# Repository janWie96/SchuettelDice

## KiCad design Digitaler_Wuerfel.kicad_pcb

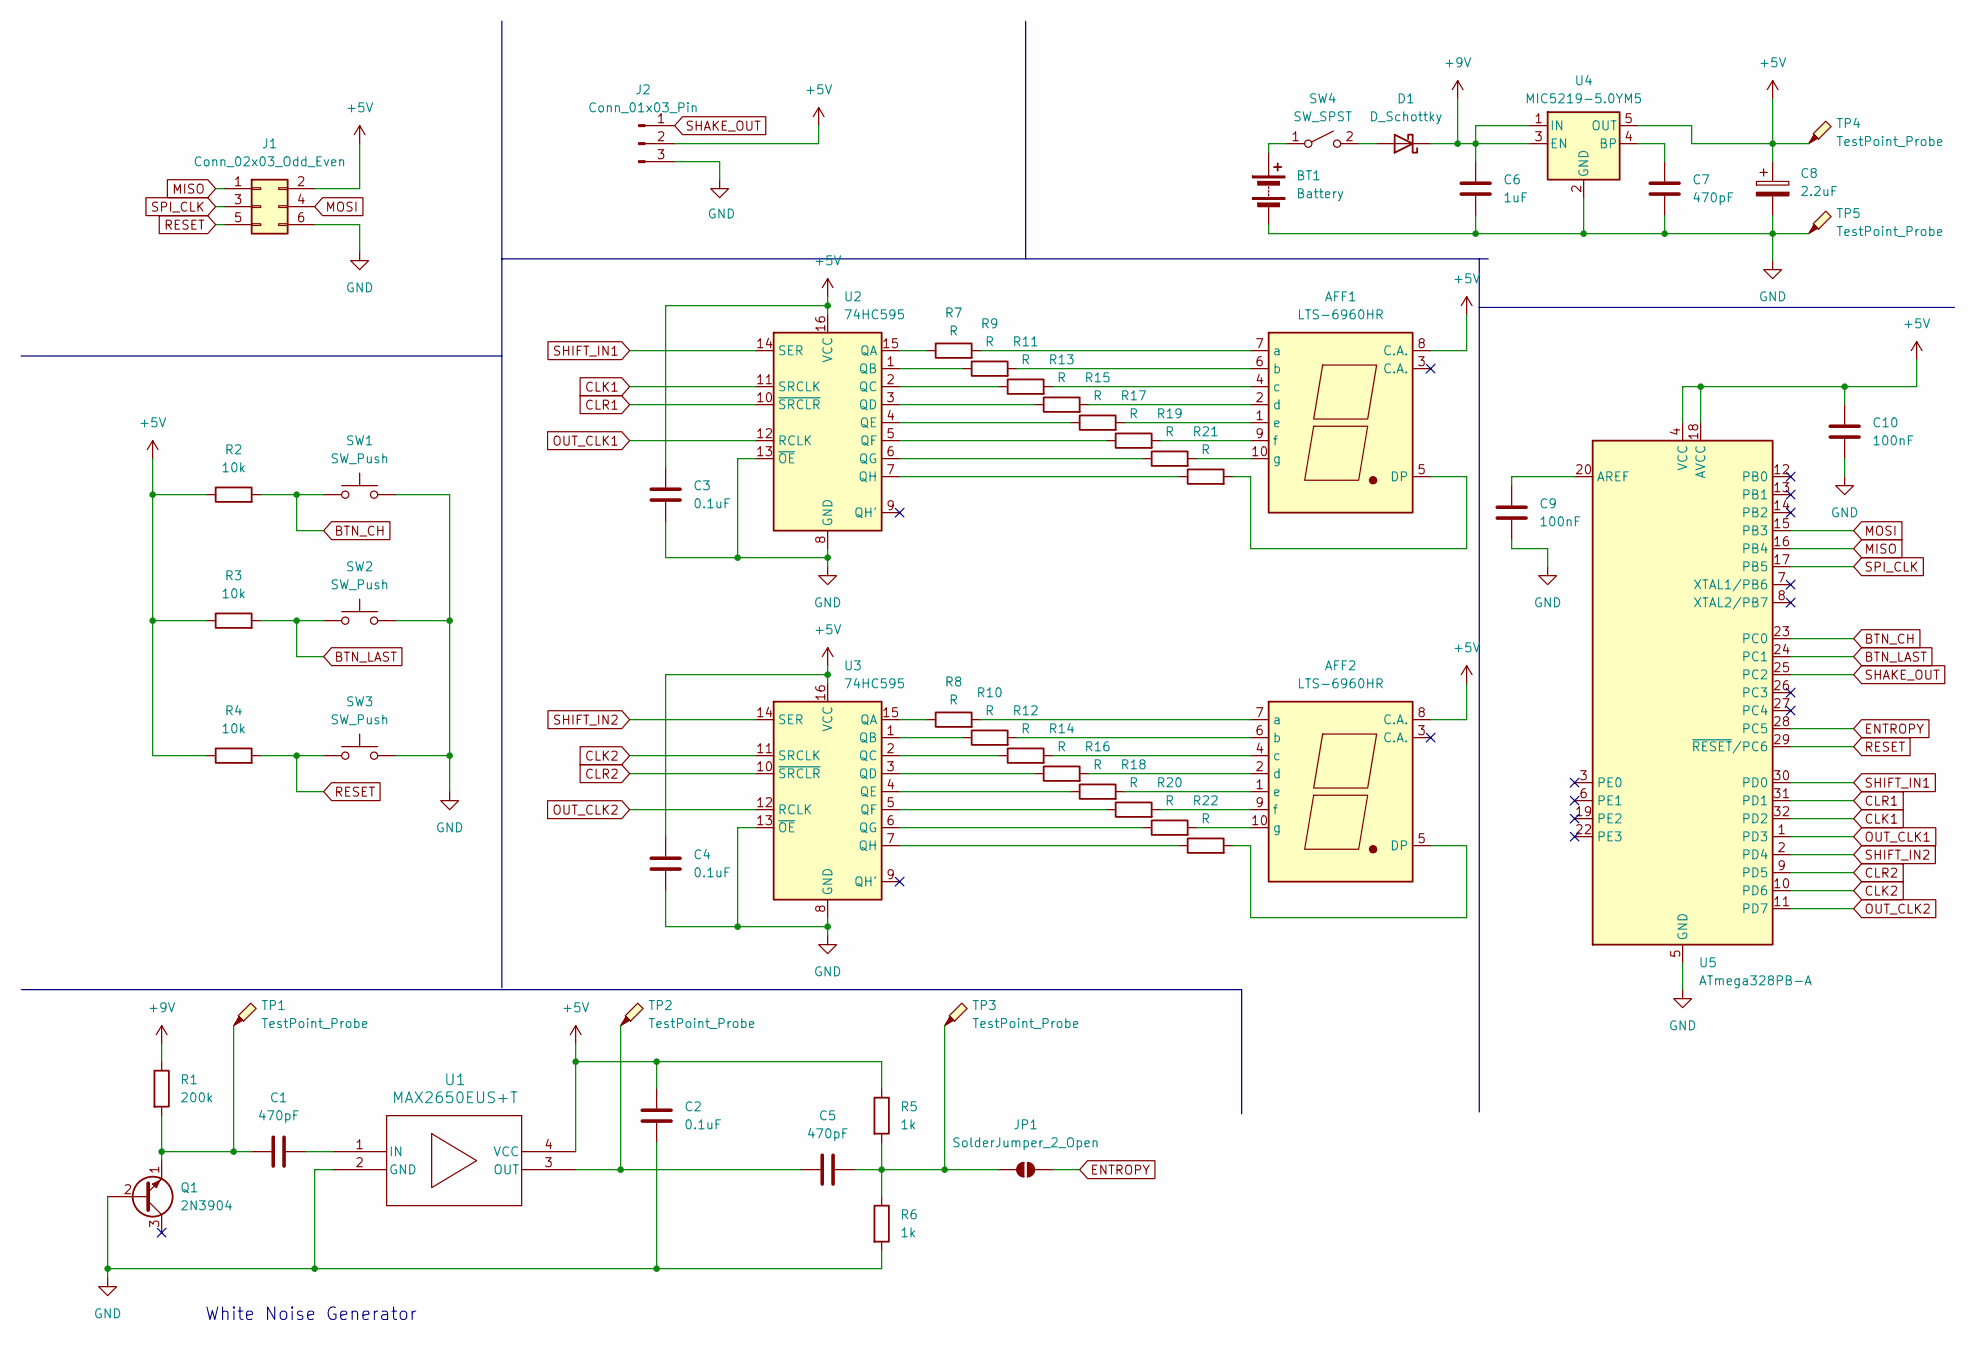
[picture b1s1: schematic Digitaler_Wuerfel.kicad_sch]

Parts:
AFF1, AFF2: LTS-6960HR; 7SegmentLED_LTS6760_LTS6780
BT1: Battery; BatteryHolder_Eagle_12BH611-GR
C1, C5, C7: 470pF; C_0805_2012Metric_Pad1.18x1.45mm_HandSolder
C2, C3, C4: 0.1uF; C_0805_2012Metric_Pad1.18x1.45mm_HandSolder
C6: 1uF; C_0805_2012Metric_Pad1.18x1.45mm_HandSolder
C8: 2.2uF; CP_EIA-3528-21_Kemet-B_Pad1.50x2.35mm_HandSolder
C9, C10: 100nF; C_0805_2012Metric_Pad1.18x1.45mm_HandSolder
D1: D_Schottky; D_SOD-323_HandSoldering
J1: Conn_02x03_Odd_Even; PinHeader_2x03_P2.54mm_Vertical
J2: Conn_01x03_Pin; PinHeader_1x03_P2.54mm_Vertical
JP1: SolderJumper_2_Open; SolderJumper-2_P1.3mm_Open_TrianglePad1.0x1.5mm
Q1: 2N3904; TO-92_Inline
R1: 200k; R_0805_2012Metric_Pad1.20x1.40mm_HandSolder
R2, R3, R4: 10k; R_0805_2012Metric_Pad1.20x1.40mm_HandSolder
R5, R6: 1k; R_0805_2012Metric_Pad1.20x1.40mm_HandSolder
R7, R8, R9, R10, R11, R12, R13, R14, R15, R16, R17, R18, R19, R20, R21, R22: R; R_0805_2012Metric_Pad1.20x1.40mm_HandSolder
SW1, SW2: SW_Push; SW_PUSH-12mm_Wuerth-430476085716
SW3: SW_Push; SW_PUSH_6mm_H5mm
SW4: SW_SPST; SW_E-Switch_EG1271_SPDT
TP1, TP2, TP3, TP4, TP5: TestPoint_Probe; TestPoint_Pad_D2.0mm
U1: MAX2650EUS+T; 21-0052F_MXM
U2, U3: 74HC595; DIP-16_W7.62mm
U4: MIC5219-5.0YM5; SOT-23-5
U5: ATmega328PB-A; TQFP-32_7x7mm_P0.8mm

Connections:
+5V: AFF1.8 (C.A.), AFF2.8 (C.A.), C2.2, C3.1, C4.1, C8.1, C10.1, J1.2, J2.2, R2.1, R3.1, R4.1, R5.1, TP4.1, U1.4 (VCC), U2.16 (VCC), U3.16 (VCC), U4.5 (OUT), U5.4 (VCC), U5.18 (AVCC)
+9V: C6.1, D1.1 (K), R1.1, U4.1 (IN), U4.3 (EN)
BTN_CH: R2.2, SW1.1, U5.23 (PC0)
BTN_LAST: R3.2, SW2.1, U5.24 (PC1)
CLK1: U2.11 (SRCLK), U5.32 (PD2)
CLK2: U3.11 (SRCLK), U5.10 (PD6)
CLR1: U2.10 (~SRCLR), U5.31 (PD1)
CLR2: U3.10 (~SRCLR), U5.9 (PD5)
ENTROPY: JP1.2 (B), U5.28 (PC5); also elsewhere on the board
GND: BT1.2 (-), C2.1, C3.2, C4.2, C6.2, C7.2, C8.2, C9.2, C10.2, J1.6, J2.3, Q1.2 (B), R6.2, SW1.2, SW2.2, SW3.2, TP5.1, U1.2 (GND), U2.8 (GND), U2.13 (~OE), U3.8 (GND), U3.13 (~OE), U4.2 (GND), U5.5 (GND), U5.21 (GND)
MISO: J1.1, U5.16 (PB4)
MOSI: J1.4, U5.15 (PB3)
unnamed: AFF1.5 (DP), R21.2
unnamed: AFF1.7 (a), R7.2
unnamed: AFF1.6 (b), R9.2
unnamed: AFF1.4 (c), R11.2
unnamed: AFF1.2 (d), R13.2
unnamed: AFF1.1 (e), R15.2
unnamed: AFF1.9 (f), R17.2
unnamed: AFF1.10 (g), R19.2
unnamed: AFF2.5 (DP), R22.2
unnamed: AFF2.7 (a), R8.2
unnamed: AFF2.6 (b), R10.2
unnamed: AFF2.4 (c), R12.2
unnamed: AFF2.2 (d), R14.2
unnamed: AFF2.1 (e), R16.2
unnamed: AFF2.9 (f), R18.2
unnamed: AFF2.10 (g), R20.2
unnamed: BT1.1 (+), SW4.1 (A)
unnamed: D1.2 (A), SW4.2 (B)
unnamed 30: C5.2, JP1.1 (A), R5.2, R6.1, TP3.1; also elsewhere on the board
unnamed: C1.1, Q1.1 (E), R1.2, TP1.1
unnamed: C1.2, U1.1 (IN)
unnamed: C5.1, TP2.1, U1.3 (OUT)
unnamed: R7.1, U2.15 (QA)
unnamed: R9.1, U2.1 (QB)
unnamed: R11.1, U2.2 (QC)
unnamed: R13.1, U2.3 (QD)
unnamed: R15.1, U2.4 (QE)
unnamed: R17.1, U2.5 (QF)
unnamed: R19.1, U2.6 (QG)
unnamed: R21.1, U2.7 (QH)
unnamed: R8.1, U3.15 (QA)
unnamed: R10.1, U3.1 (QB)
unnamed: R12.1, U3.2 (QC)
unnamed: R14.1, U3.3 (QD)
unnamed: R16.1, U3.4 (QE)
unnamed: R18.1, U3.5 (QF)
unnamed: R20.1, U3.6 (QG)
unnamed: R22.1, U3.7 (QH)
unnamed: C7.1, U4.4 (BP)
unnamed: C9.1, U5.20 (AREF)
OUT_CLK1: U2.12 (RCLK), U5.1 (PD3)
OUT_CLK2: U3.12 (RCLK), U5.11 (PD7)
RESET: J1.5, R4.2, SW3.1, U5.29 (~RESET/PC6)
SHAKE_OUT: J2.1, U5.25 (PC2)
SHIFT_IN1: U2.14 (SER), U5.30 (PD0)
SHIFT_IN2: U3.14 (SER), U5.2 (PD4)
SPI_CLK: J1.3, U5.17 (PB5)

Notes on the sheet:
White Noise Generator

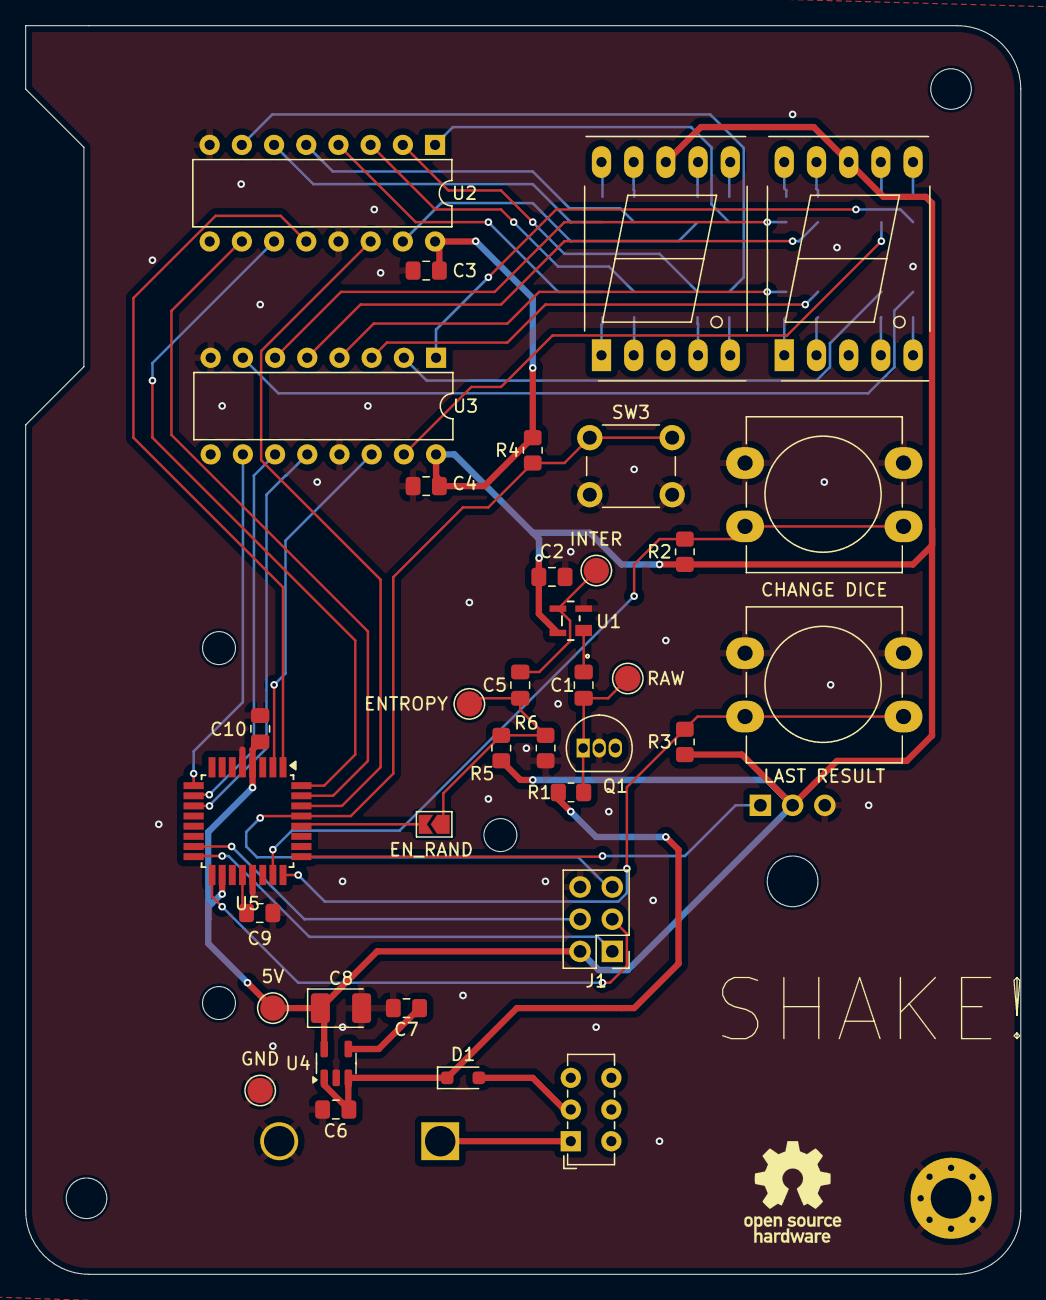
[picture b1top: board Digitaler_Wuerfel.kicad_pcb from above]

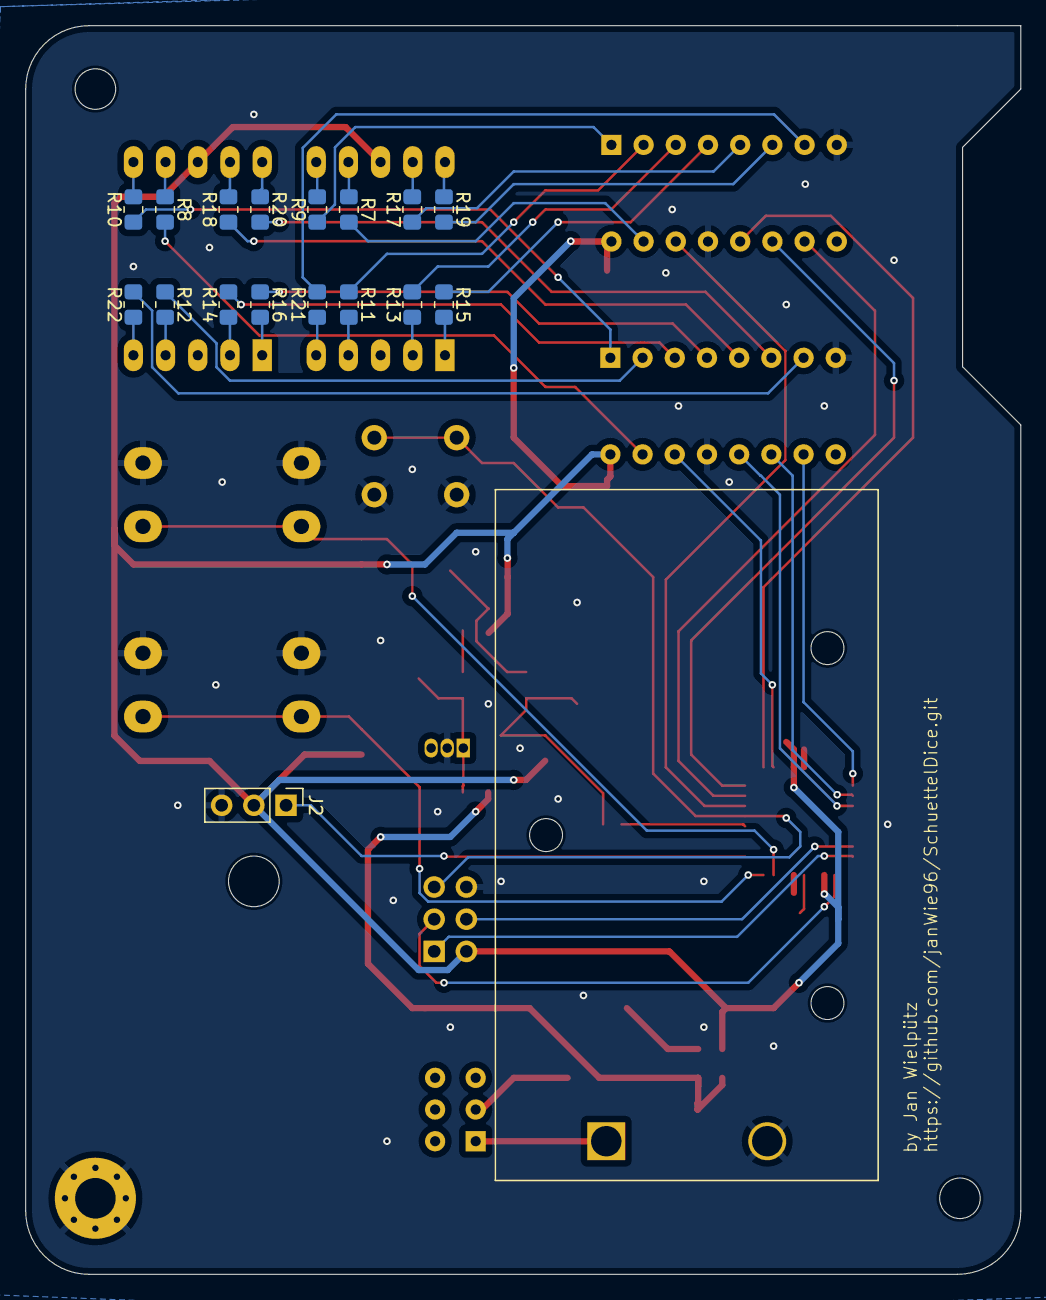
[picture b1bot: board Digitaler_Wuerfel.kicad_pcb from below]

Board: 2 copper layers, 78.5 x 98.5 mm, 54 parts (18 on the bottom side), 59 nets.

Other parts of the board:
EN_RAND: SolderJumper_2_Open; SolderJumper-2_P1.3mm_Open_TrianglePad1.0x1.5mm

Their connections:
ENTROPY: EN_RAND.2 (B); also elsewhere on the board
unnamed 30: EN_RAND.1 (A); also elsewhere on the board

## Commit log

2025-01-22 Started tracing
2025-01-23 Finished tracing
2025-01-23 Corrected ditch
2025-01-23 Added decoupling capacitors and ground plane
2025-01-23 Into production
